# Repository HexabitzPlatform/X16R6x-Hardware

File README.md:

# X16R6x-Hardware
Hexabitz LED Matrix Interface Module Hardware Design

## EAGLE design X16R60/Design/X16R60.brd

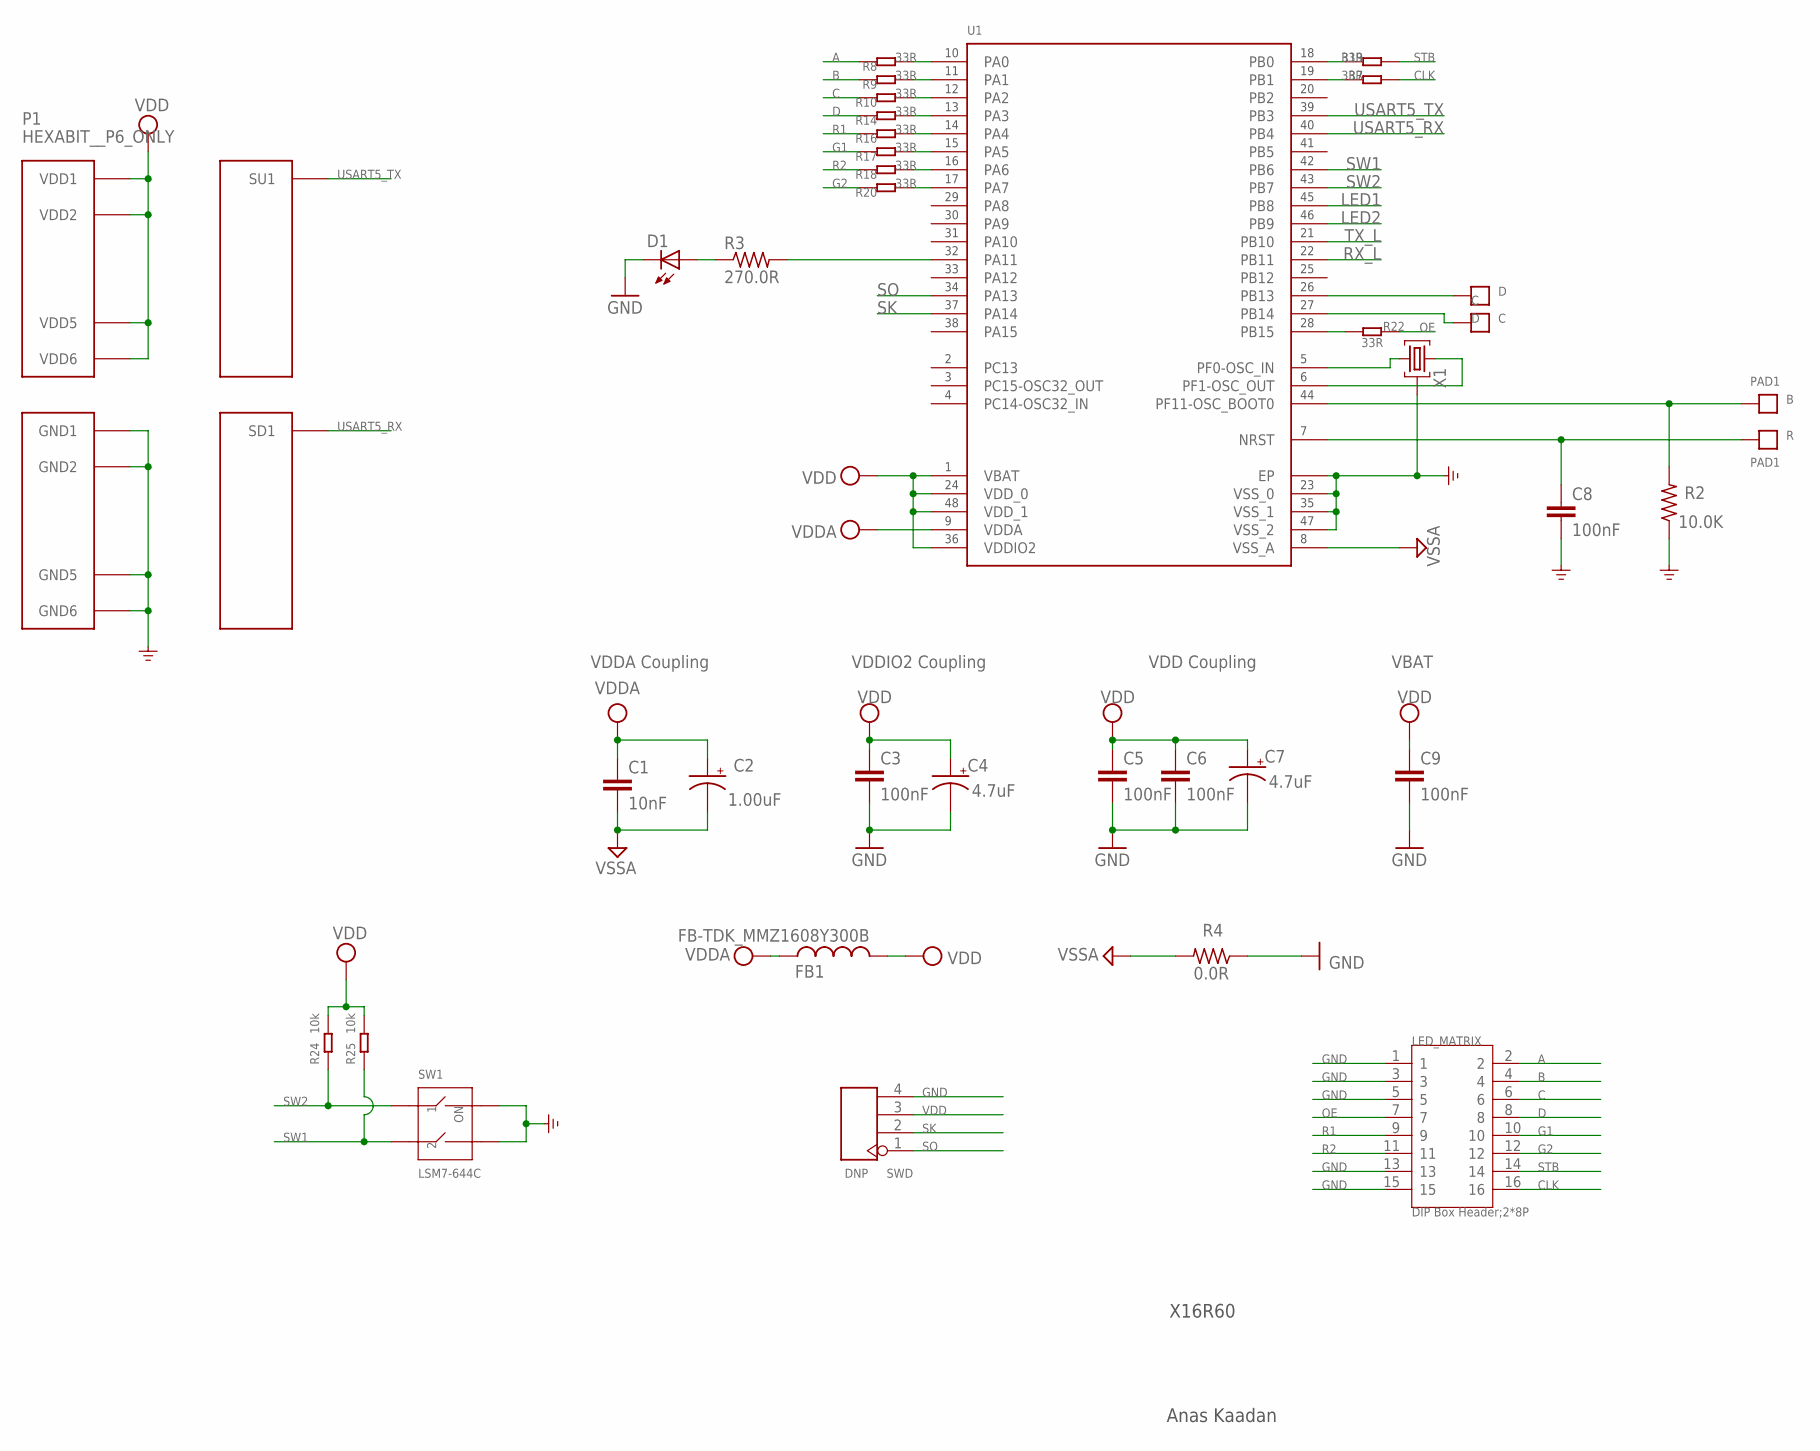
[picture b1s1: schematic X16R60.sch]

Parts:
B: PAD1
C: C; PAD1
C1: 10nF; C-0603; TOLERANCE 10%; VOLTAGE_RATING 50V; MPN C0603C103K5RACTU
C2: 1.00uF; C-0805-POL; TOLERANCE 10%; VOLTAGE_RATING 16V; MPN CC0805KKX7R7BB105
C3, C6, C8: 100nF; C-0603; TOLERANCE 10%; VOLTAGE_RATING 10V; MPN C0603C104K8RACTU
C4, C7: 4.7uF; C-0805-POL; TOLERANCE 10%; VOLTAGE_RATING 25V; MPN GRM21BC81E475KA12L
C5: 100nF; C-0603; TOLERANCE 10%; VOLTAGE_RATING 10; MPN C0603C104K8RACTU
C9: 100nF; C-0603; TOLERANCE 10V; VOLTAGE_RATING 10%; MPN C0603C104K8RACTU
D: D; PAD1
D1: VLMS1300-GS08; MPN VLMS1300-GS08
FB1: FB-TDK_MMZ1608Y300B; MPN MMZ1608Y300B
LED_MATRIX: DIP Box Header;2*8P; H2X8_2.54
P1: HEXABIT__P6_ONLY; HEXABIT_17.32_P6_ONLY
R: PAD1
R2: 10.0K; R-0603; TOLERANCE 5%; MPN RC0603JR-0710KL
R3: 270.0R; R-0603; TOLERANCE 1%; MPN RC0603FR-07270RL
R4: 0.0R; R-0603; MPN RC0603JR-070RL
R7, R8, R9, R10, R14, R16, R17, R18, R19, R20, R22: 33R; R0402; MPN AC0402FR-0733RL
R24, R25: 10k; R0402; MPN RC0402FR-07510KL
SW1: LSM7-644C; SW4-SMD-2.54-5.08X6.8X3.3MM; MPN KAE02LGGR
SWD: DNP; H4-2.54
U1: STM32F091CBU6
X1: XTALL_CSTCE8M00G52

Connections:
A: LED_MATRIX.2, R8.1
B: LED_MATRIX.4, R9.1
B1: B.P$1, B.P$2, R2.2, U1.P$44 (PF11-OSC_BOOT0)
C: LED_MATRIX.6, R10.1
CLK: LED_MATRIX.16, R7.2
D: LED_MATRIX.8, R14.1
G1: LED_MATRIX.10, R17.1
G2: LED_MATRIX.12, R20.2
GND: C3.2, C4.2 (-), C5.2, C6.2, C7.2 (-), C8.2, C9.2, D1.C, LED_MATRIX.1, LED_MATRIX.3, LED_MATRIX.5, LED_MATRIX.13, LED_MATRIX.15, P1.PAD_PD8 (GND1), P1.PAD_PD9 (GND2), P1.PAD_PD10 (GND5), P1.PAD_PD11 (GND6), R2.1, R4.1, SW1.3, SW1.4, SWD.4, U1.EP, U1.P$23 (VSS_0), U1.P$35 (VSS_1), U1.P$47 (VSS_2), X1.P$2 (2)
LED1: U1.P$45 (PB8)
LED2: U1.P$46 (PB9)
unnamed: U1.P$5 (PF0-OSC_IN), X1.P$1 (1)
unnamed: R14.2, U1.P$13 (PA3)
unnamed: R8.2, U1.P$10 (PA0)
unnamed: U1.P$6 (PF1-OSC_OUT), X1.P$3 (3)
unnamed: R16.2, U1.P$14 (PA4)
unnamed: R17.2, U1.P$15 (PA5)
unnamed: R18.2, U1.P$16 (PA6)
unnamed: R9.2, U1.P$11 (PA1)
unnamed: R10.2, U1.P$12 (PA2)
unnamed: R20.1, U1.P$17 (PA7)
unnamed: R19.1, U1.P$18 (PB0)
unnamed: D1.A, R3.1
unnamed: R22.1, U1.P$28 (PB15)
unnamed: R3.2, U1.P$32 (PA11)
unnamed: D.P$1, D.P$2, U1.P$26 (PB13)
unnamed: C.P$1, C.P$2, U1.P$27 (PB14)
unnamed: R7.1, U1.P$19 (PB1)
OE: LED_MATRIX.7, R22.2
R1: LED_MATRIX.9, R16.1
R2: LED_MATRIX.11, R18.1
R3: C8.1, R.P$1, R.P$2, U1.P$7 (NRST)
RX_L: U1.P$22 (PB11)
SK: SWD.2, U1.P$37 (PA14)
SO: SWD.1, U1.P$34 (PA13)
STB: LED_MATRIX.14, R19.2
SW1: R25.1, SW1.2, U1.P$42 (PB6)
SW2: R24.1, SW1.1, U1.P$43 (PB7)
TX_L: U1.P$21 (PB10)
USART5_RX: P1.PAD_PD3 (SD1), U1.P$40 (PB4)
USART5_TX: P1.PAD_PU3 (SU1), U1.P$39 (PB3)
VDD: C3.1, C4.1 (+), C5.1, C6.1, C7.1 (+), C9.1, FB1.2, P1.PAD_PU8 (VDD1), P1.PAD_PU9 (VDD2), P1.PAD_PU10 (VDD5), P1.PAD_PU11 (VDD6), R24.2, R25.2, SWD.3, U1.P$1 (VBAT), U1.P$24 (VDD_0), U1.P$36 (VDDIO2), U1.P$48 (VDD_1)
VDDA: C1.1, C2.1 (+), FB1.1, U1.P$9 (VDDA)
VSSA: C1.2, C2.2 (-), R4.2, U1.P$8 (VSS_A)

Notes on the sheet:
X16R60
Anas Kaadan
VDDA Coupling
VDDIO2 Coupling
VDD Coupling
VBAT

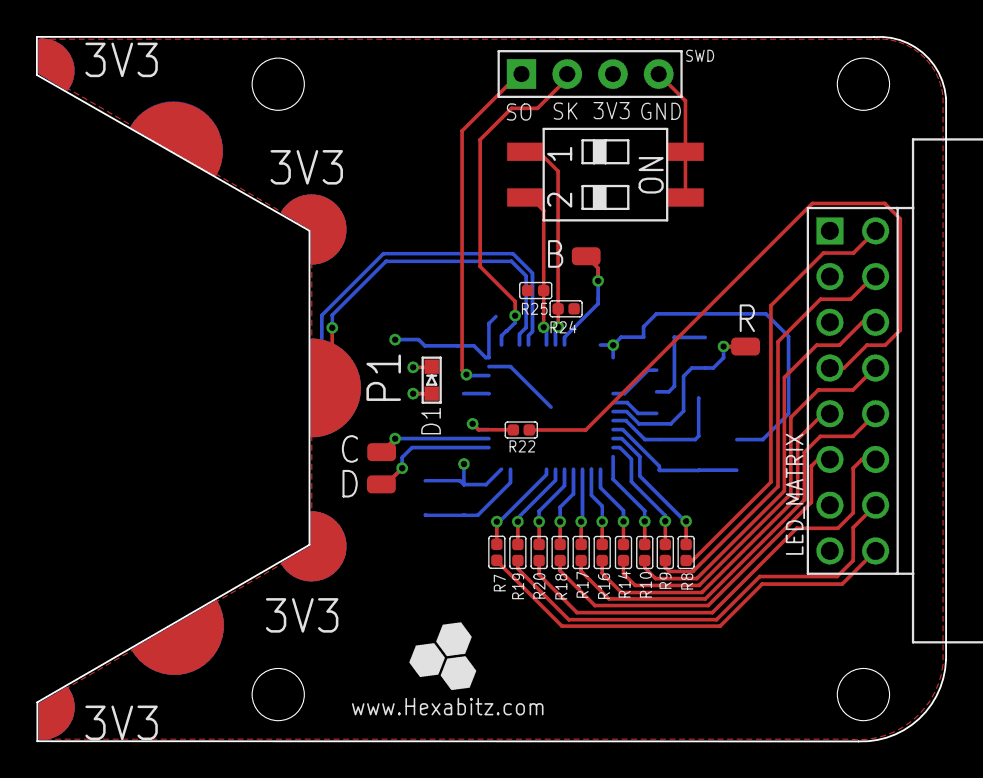
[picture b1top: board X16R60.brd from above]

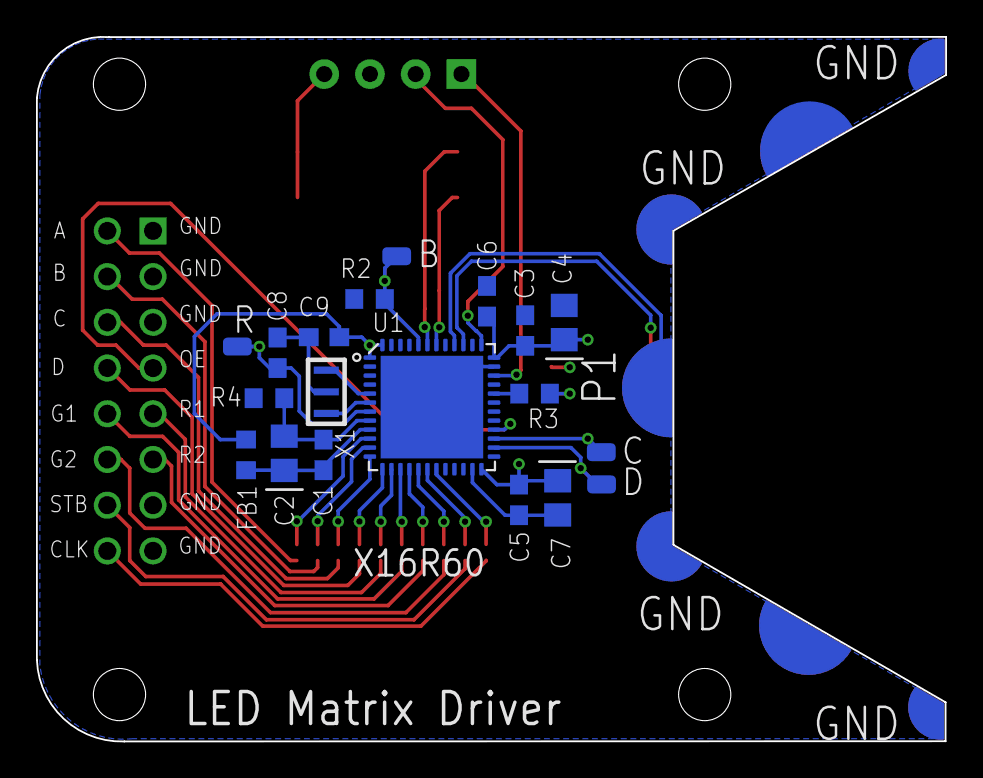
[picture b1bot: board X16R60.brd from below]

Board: 2 copper layers, 50.5 x 39.1 mm, 37 parts (18 on the bottom side), 40 nets.

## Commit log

2021-04-18 - All output files were generated..
2021-04-18 changed the folder name to X16R60
2021-04-21 Updated BOM..
2021-04-22 - Updated BOM..
2021-04-25 - Changed MCU.. - Deleted unnecessary components.. - Regenerated output files.. - Updated BOM.. - Updated Batch_4_21 on google docs..
2021-04-26 Final..
